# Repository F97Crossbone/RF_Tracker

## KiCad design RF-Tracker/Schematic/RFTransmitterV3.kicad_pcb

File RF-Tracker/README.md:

# RF Tracker

### Directory Structure:
- `common/`: Additional library files for the SI 4010
- `docs/`: Documentation images.
- `Schematic/`: Contains all files for the schematic and PCB
- `Software/`: Contains all files for the actual software running on the SI4010 embedded system
    - `bin/`: Project files
    - `out/`: Output files
    - `src/`: The actual code
---

### Assembly Instructions:
Make sure you have all the components listed in [Bill of Materials](ShitboxV4_BOM.xls). Other required componenets and materials not part of the BOM:
- 1x 1x2 2.54mm pitch male header
- 1x 2x5 2.54mm pitch male header
- 1x CR2477 (Any 3.3v battery can be used, but a different battery holder will be required).

#### Assembly steps:
1. Solder the SI 4010 ensuring pin 1 lines up with the astericks on the board.
2. Solder the LEDs, referencing the BOM for placement.
3. Solder the remaining passives, referencing the BOM for placement. The inductor must be soldered on the L1 pad.
4. Solder the button to channel select pad.
5. Solder the headers to the board
6. Solder the battery holder, using the silkscreen markings for orientation.
7. Cut an antenna wire using the instructions below and solder it to the AE1 pad.

#### Antenna Cutting:
If you plan on operating on the 216MHz band, the antenna wire should be 22 gauge and 4.5cm long. If you plan on operating in another band, use [this calculator](https://m0ukd.com/calculators/loaded-quarter-wave-antenna-inductance-calculator/) to determine antenna wire length. Input the frequency in MHz, 0.01 in the coil position field, and 0.6426 in the wire diameter field. You'll then want to input distance values and press the design button until the inductance value is very close to 1µH.

**DISCLAMER:** DO NOT USE A FREQUENCY IF YOU DO NOT HAVE A LICENSE FOR IT.

### Programming & Burning Instructions:
This requires a Windows machine. If you are running on MacOS or Linux, you'll need to use a virtual machine or use a machine with windows installed on it.

You'll also need to connect the Silicon Labs USB Debug Adapter to your PC with a USB-B cable.

You will need to download various software packages to burn the code to the tracker:
- [Silicon Labs IDE](https://www.silabs.com/developers/8-bit-8051-microcontroller-software-studio)
- [Silicon Labs Burn Tools](http://www.silabs.com/Support%20Documents/Software/Si4010_Burn_Tools.exe) * - Note: The *
- [Keil PK51](https://developer.arm.com/Tools%20and%20Software/Keil%20PK51) *- Note: you'll need to input some personal information for this one. There is also an option to purchase the software for commercial use, don't click on that.*

#### Programming and burning steps:
1. Navigate the [Software](Software/bin) folder and open `RF_Tracker.wsp`. This will open the Silicon Labs IDE.
    1. If you are operating on a different band, navigate to the `RF_Tracker.h` file and change the `FREQUENCY` number to the desired frequency in Hz. If you desire to change the channel separation, that is located below and also is also in Hz. **Ensure the numbers end in .0 to avoid issues.**
2. Once the IDE has opened, build the project by clicking the `Compile All` button.  

3. The console at the bottom of the screen should display `OBJECT TO HEXT CONVERSION COMPLETED` if successful.
4. Once the project has been built, put a battery in the RF Tracker and connect the USB Debug adapter to the programming header, making sure the red wire lines up with the `RED GO HERE` text on the PCB. 
5. Open `Si4010_NVM_Burner.exe`, which should have been installed to `C:\SiLabs\MCU\Si4010_NVMProgUtil`
6. Once open, select the USB Debug Adapter from the dropdown menu and press connect.
7. Once connected, press the `New` button next to `NVM Burn File`. Just press save with the default location and name.  

8. Then click `Add` next to `User Boot files`. Navigate to the [Output folder](Software/out/) and select `RF_tracker.hex`
9. Once the file has been added, select the following flags  

10. Press `Compose`.
11. Once composed, connect 6.5v and GND to the 1x2 header on the PCB and press `Burn`. Remove the 6.5v connection once burned to avoid overvolting and cooking the SI4010.
12. Press the disconnect button and remove the USB Debug Adapter from the programming header. The board should be functioning.

### Using the tracker:
The tracker will start up running on channel 1 (if the code is unmodified, this is 216MHz). The default channel separation is 50kHz. The tracker will transmit once a second. This is indicated by the transmit LED.

If you wish the see the channel the tracker is on, press (don't hold!) the channel select button. The channel LED will blink to indicate the selected channel. For example, if the tracker is on channel 3, the LED will blink 3 times.

Changing the channel works as follows:
1. Hold the `Channel Select` button for at least 5 seconds to enter the channel selction mode. Release the button.
    1. While in channel select mode, the tracker will not transmit.
2. The channel LED should now be blinking rapidly. Press the button to increment the channel. If you want to be on channel 3, press the button 3 times. 5 times for channel 5, etc.
3. Once complete, hold the channel select button for 5 seconds to exit channel select mode. Upon exiting, the channel LED will blink to indicate the selected channel. The tracker will start transmitting on the new channel automatically.
    1. If you did not select a channel, the tracker will default to channel 1.

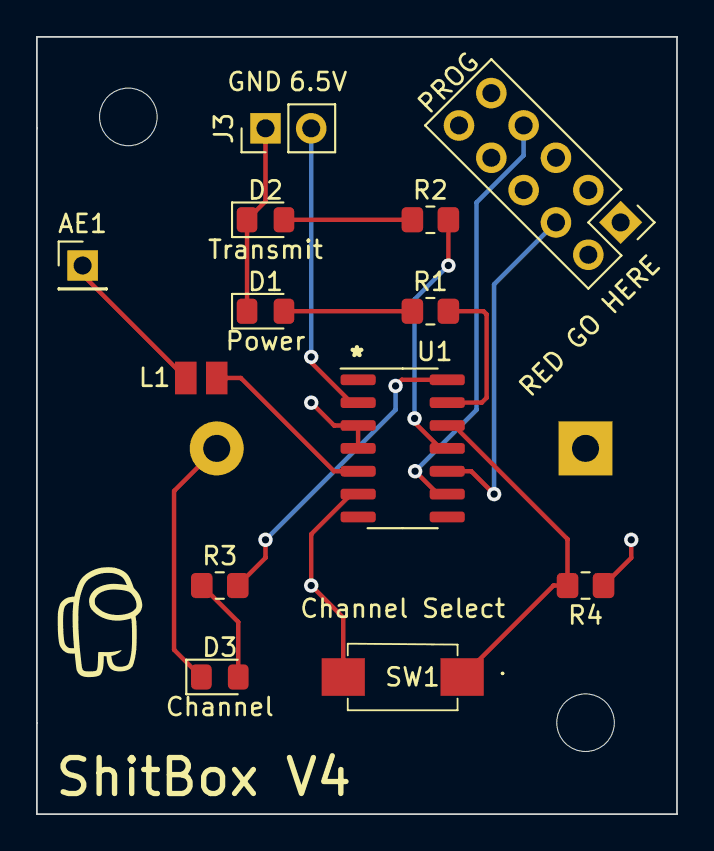
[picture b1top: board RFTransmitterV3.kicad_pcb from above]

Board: 4 copper layers, 35.6 x 43.2 mm, 15 parts (1 on the bottom side), 14 nets.

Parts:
AE1: Antenna; PinHeader_1x01_P2.54mm_Vertical
BT1: 3.33v Coincell; BatteryHolder_Keystone_105_1x2430
D1: Power; LED_0805_2012Metric_Pad1.15x1.40mm_HandSolder
D2: Transmit; LED_0805_2012Metric_Pad1.15x1.40mm_HandSolder
D3: Channel; LED_0805_2012Metric_Pad1.15x1.40mm_HandSolder
G0: LOGO; amongus_small
J3: 6.5v Programming Connector; PinHeader_1x02_P2.54mm_Vertical
L1: 1uH; INDC2016X100N
PROG: ProgrammingAdapter; PinHeader_2x05_P2.54mm_Vertical
R1, R2, R3, R4: 1k; R_0805_2012Metric_Pad1.20x1.40mm_HandSolder
SW1: SW_ChnlSelect; PTS636SM25FSMTRLFS
U1: Si4010-GS; SOIC-14_3.9x8.7mm_P1.27mm

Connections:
+3V3: BT1.1 (+), SW1.2, U1.6
/C2CLK: PROG.7, U1.9
/C2DAT: PROG.4, U1.10
/TXP: L1.2, U1.5
/VPP: J3.2, U1.2
GND: BT1.2 (-), D1.1 (K), D2.1 (K), D3.1 (K), J3.1, PROG.2, R4.1, U1.3, U1.4
GPIO1: R1.2, U1.13
GPIO2: R4.2, SW1.1, U1.12
GPIO3: R2.2, U1.11
GPIO8: R3.2, U1.14
unnamed: AE1.1 (A), L1.1
unnamed: D1.2 (A), R1.1
unnamed: D2.2 (A), R2.1
unnamed: D3.2 (A), R3.1

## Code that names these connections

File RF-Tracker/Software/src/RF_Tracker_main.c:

/*------------------------------------------------------------------------------
 *                          Silicon Laboratories, Inc.
 *                           http://www.silabs.com
 *                               Copyright 2010
 *------------------------------------------------------------------------------
 *
 *    FILE:       tone_demo_main.c
 *    TARGET:     Si4010
 *    TOOLCHAIN:  Generic
 *    DATE:       January 18, 2023, Wednesday
 *    RELEASE:    2.1 (MPech), ROM version 02.00, trim 3
 *
 *------------------------------------------------------------------------------
 *
 *    DESCRIPTION:
 *      This file contains the main function for the tone demo.
 *      It MUST be run on properly trim part!
 *
 *      Then it tracks frequency with temperature by fine tuning
 *      process by repeatedly calling the vStl_SingleTxLoop() function.
 *      Ultimately, if the temperature is going to drift too much
 *      from what it was during the main tuning vFCast_Tune()
 *      call then the fine tuning process will not be able
 *      to properly track the output frequency with temperature.
 *
 *      For an example how to interrupt to CW tone output after
 *      predefined time, retune by vFCast_Tune(), and start transmitting
 *      tone again see the tone_demo_ptune_main.c for periodic tuning.
 *
 *------------------------------------------------------------------------------
 *
 *    INCLUDES:
 */
#include <stdlib.h>
#include "si4010.h"
#include "si4010_api_rom.h"

#include "RF_Tracker.h"


/*------------------------------------------------------------------------------
 *
 *    FUNCTION DESCRIPTION:
 *      Main function for the example.
 *
 *------------------------------------------------------------------------------
 */

void    main(void)
{

//Set DMD interrupt to high priority,
// any other interrupts have to stay low priority
  PDMD=1;
// Disable the Matrix and Roff modes 
  PORT_CTRL &= ~(M_PORT_MATRIX | M_PORT_ROFF | M_PORT_STROBE);
  PORT_CTRL |=  M_PORT_STROBE;
  PORT_CTRL &= ~M_PORT_STROBE;

  /* clear master time */
  vSys_SetMasterTime( 0UL );

  // button setup
  bsrSetup.bButtonMask = (1 << B_GPIO2);
  bsrSetup.pbPtsReserveHead = (BYTE *) ptsArray;
  bsrSetup.bPtsSize = PTS_SIZE;
  bsrSetup.bPushQualThresh = 3;

  vBsr_Setup(&bsrSetup);

  /* Setup the RTC to tick every 5ms and clear it. Keep it disabled. */
  RTC_CTRL = (0x07 << B_RTC_DIV) | M_RTC_CLR;

  RTC_CTRL |= M_RTC_ENA;
  /* Enable the RTC interrupt and global interrupt enable */
  ERTC = 1;
  EA = 1;

// LED control bit off 
  GPIO_LED = 0;

// Enable Power LED
  GPIO1 = 1;
// Disable Channel LED
  GPIO8 = 0;

  // state vars
  holdStart = 0;
  changingChannel = 0;

  mode = 0;

  channel = 1;
  readback = 1;

// Call the system setup. This just for initialization.
// Argument of 1 just configures the SYS module such that the
// bandgap can be turned off if needed.  
  vSys_Setup( 1 );

// Setup the bandgap for working with the temperature sensor here.
// bSys_FirstBatteryInsertWaitTime set to non zero value. 
  vSys_BandGapLdo( 1 );

// PA setup.
// fAlpha and fBeta has to be set based on antenna configuration.
// Chose a PA level and nominal cap. Both values come from
// the calculation spreadsheet. 
  rPaSetup.fAlpha      = 0.0;
  rPaSetup.fBeta       = 0.3387;
  rPaSetup.bLevel      = 36;
  rPaSetup.wNominalCap = 10;
  rPaSetup.bMaxDrv     = 0;

// PA setup 
  vPa_Setup( &rPaSetup );

// ODS setup .. results from calculation spreadsheet.
// Set to 1kbps OOK 
  rOdsSetup.bModulationType = 0; // 1 .. FSK, 0 .. OOK 
  rOdsSetup.bClkDiv         = 5;
  rOdsSetup.bEdgeRate       = 0;

// Set group width to 7, which means 8 bits/encoded byte to be transmitted.
// The value must match the output width of the data encoding function
// set by the vStl_EncodeSetup() below. 
  rOdsSetup.bGroupWidth     = 7;
  rOdsSetup.wBitRate        = 4000;  // 1kbps 

// Configure the warm up intervals LC: 8, DIV: 5, PA: 4 
  rOdsSetup.bLcWarmInt  = 8;
  rOdsSetup.bDivWarmInt = 5;
  rOdsSetup.bPaWarmInt  = 4;

// ODS setup 
  vOds_Setup( &rOdsSetup );

// Setup the STL encoding for none. No encode function therefore we
// leave the pointer at NULL. 
  vStl_EncodeSetup( bEnc_NoneNrz_c, NULL );

// Generate the frame to use. Example array is fixed in CODE
// as constant for this example. Assign the beginning of the array
// to the pbFrameHead pointer. 
  pbFrameHead = (BYTE xdata *) abTone_FrameArray;

// Setup frequency casting .. needed to be called once per boot 
  vFCast_Setup();

// Run at 216.xxx MHz.  Continue to tune frequency between frames.
// This is not absolutely necessary as the Single transmission loop
// also adjusts for temperature drift. It calculate values used by
// the vStl_SingleTxLoop() during transmission. Input is in [Hz]. 
  vFCast_Tune( FREQUENCY + (channel * CHANNEL_SEP) );

// Call vFCast_FskAdj with the maximum FSK adjustment.
// Input parameter value comes from the calculation spreadsheet.
// We are not running FSK for tone. 

// Now wait until there is a demodulated temperature sample  
  while ( 0 == bDmdTs_GetSamplesTaken() ){}

// Tune the PA with the current temperature as an argument 
  vPa_Tune( iDmdTs_GetLatestTemp() );

// -- Run the Single Tx Loop 
  vStl_PreLoop( );

// Encoding is none .. 0. Force first byte to turn the PA on.
// Set the all 1's output if there is no data .. value 3 below. 
  ODS_CTRL = (ODS_CTRL & (~M_ODS_SHIFT_CTRL)) | (3 << B_ODS_SHIFT_CTRL);

// Infinite loop, we are sending packets every second on the specified channel
  while ( 1 )
  {	
  	// button handling
	if (bBsr_GetPtsItemCnt()) {
		ptsButton = wBsr_Pop();

		// get the current button state, masking 0x04 for the button on GPIO2
		// the if statements are inversed because the GPIO pin is pulled HIGH when the button is pressed,
		// not LOW as the documentation indicates it should be.
		buttonState = *((BYTE*)(&ptsButton)+1);
		if (!(buttonState & 0x04)) {
			// record the hold start time
			holdStart = lSys_GetMasterTime() / 1000;
		} else if (buttonState & 0x04) {
			// once we let go, check to see if we should transition to channel select mode
			switch(mode) {
			case MODE_START_CHANNEL_SELECT:
				// update the mode
				mode = MODE_CHANNEL_SELECT;
				// reset channel
				channel = 0;
				break;
			case MODE_STOP_CHANNEL_SELECT:
				// make sure channel is at least 1
				if (channel == 0) channel++;

				// readback the channel & retune the transmitter
				readbackChannel();
  				vFCast_Tune( FREQUENCY + (channel * CHANNEL_SEP) );

				// update the mode
				mode = MODE_TRANSMIT;

				break;
			case MODE_CHANNEL_SELECT: // if we are in channel select, update the channel if we short-press
				channel++;
				break;
			case MODE_TRANSMIT: // if we are in transmit mode, readback the channel if we short-press
				readbackChannel();
				break;
 			default:
				break;
			}
		}
	} else {
		buttonState = 0;
	}

	// we've held the button for 5 seconds, change the mode
	if (holdStart > 0 && lSys_GetMasterTime()/1000 - holdStart >= 5) {
		switch(mode) {
		case MODE_TRANSMIT:
			mode = MODE_START_CHANNEL_SELECT;
			holdStart = 0;
			break;
		case MODE_CHANNEL_SELECT:
			mode = MODE_STOP_CHANNEL_SELECT;
			holdStart = 0;
			break;
		default:
			break;
		}
	}

	// if we are transmitting
	if (mode == MODE_TRANSMIT) {
	  	// beep for one second, also turn LED on
		if ((lSys_GetMasterTime() / 1000) % 2 == 0){
		    vStl_SingleTxLoop( pbFrameHead,
		                       2 );  // Frame length in bytes 
		    GPIO3 = 1;
		}
		else {
			// turn LED off for one second
			GPIO3 = 0;
		}
	} else if (mode == MODE_START_CHANNEL_SELECT || mode == MODE_CHANNEL_SELECT) {
		GPIO3 = 0; // turn off transmit LED
		// rapidly flash channel LED to indicate the mode
		if ((lSys_GetMasterTime()/50)%2 == 0) {
			GPIO8=1;
		} else {
			GPIO8=0;
		}
	}
  }

// Infinite termination loop
// never reached, TODO: some way to set the chip into IDLE mode?
  while ( 1 )
  {
    PCON |= M_IDLE;
    PCON = PCON;   // Must be used after going to IDLE 
  }

// This will never happen. 
  return;
}

/**
	Reads back the currently selected channel on the channel LED.
*/
void readbackChannel() {
	readback = 0; // current readback tick
	canInc = 1; // used for delay
	GPIO3 = 0; // turn transmit led off
	while (lSys_GetMasterTime() % 1000 != 0); // prevents issues where the LED flashes too quickly
	while (readback <= channel) { // while the readback tick has not reached the current channel
		if ((lSys_GetMasterTime() / 250) % 2 == 0) { // run while we are on the 2nd or 4th quarter second
			GPIO8 = 1;
			if (canInc) { // toggle to prevent incrementing readback more than once per tick
				readback++;
				canInc = 0;
			}
		} else {
			GPIO8 = 0;
			canInc = 1;
		}
	}
	GPIO8 = 0;
	return;
}

//------------------------------------------------------------------------------
